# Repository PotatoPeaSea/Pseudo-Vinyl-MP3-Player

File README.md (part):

# Pseudo Vinyl MP3 Player

A portable, battery-powered MP3 player built on the **ESP32-WROVER N4R8** that streams audio wirelessly to Bluetooth earbuds and features a **vinyl-style spinning album art** animation on a circular display.

> [!NOTE]
> **Why the classic ESP32 and not the S3?** The project originally targeted the ESP32-S3, but the S3 only has BLE — **no Bluetooth Classic**, which A2DP audio streaming requires. The original ESP32 is the only chip in the family that can act as an A2DP source. The board started on a **WROOM-32** (no PSRAM, a hard ~250–290KB working-heap budget — see [`docs/MEMORY.md`](docs/MEMORY.md) for everything that constraint drove) and later moved to a **WROVER N4R8**, same classic-ESP32 die plus **8MB PSRAM**, which is now the current hardware target. Audio output is **Bluetooth-only** — the wired PCM5102 DAC path from early prototyping was removed once the BT stack needed the RAM it occupied, and hasn't come back now that PSRAM is available (out of scope, not a technical blocker).

## Features

- **Bluetooth Audio** — Streams to wireless earbuds/speakers via A2DP, with on-device scanning, pairing, and auto-reconnect. Bluetooth is the only output — there is no wired jack.
- **Circular Display** — 1.28" GC9A01 240×240 IPS round screen
- **Vinyl Spin Animation** — Album art spins like a vinyl record during playback at a true 60fps, with a progress ring around the display edge and a drop-shadowed title for legibility over any art color
- **Physical Controls** — 3 buttons (play/pause, next, previous) + rotary encoder (volume/scroll)
- **Shuffle & Repeat** — Normal / Shuffle / Repeat All / Repeat One, cycled via encoder push
- **SD Card Storage** — Recursively scans a FAT32 SD card for MP3s; the library and playlist list load automatically at boot, before any speaker connects
- **Folder Playlists** — Top-level SD card folders are selectable playlists, alongside an always-available "All Songs" library
- **Persistent Settings** — Volume and paired Bluetooth device survive power cycles (NVS)
- **Battery Powered** — LiPo battery with TP4056 USB-C charging

## Documentation

| Document | Contents |
|---|---|
| [User Guide](docs/USER_GUIDE.md) | Getting started, controls, pairing, troubleshooting |
| [PRD](docs/PRD.md) | Original requirements/pins/risks — WROOM-32 prototype era, not updated for the WROVER pin move |
| [MEMORY.md](docs/MEMORY.md) | Canonical hardware bring-up log — every RAM/BT/audio failure found on real hardware, root cause, and fix |
| [HANDOFF.md](docs/HANDOFF.md) | What's implemented-but-not-yet-hardware-verified right now |
| This README | System architecture, build instructions |

---

## Hardware

| Component | Model | Interface |
|---|---|---|
| MCU | ESP32-WROVER N4R8 (4MB flash, 8MB PSRAM) | — |
| Display | GC9A01 1.28" Round IPS, 240×240 | SPI (GPIO-matrix routed) |
| Storage | SPI SD card reader, FAT32 | SPI (HSPI) |
| Encoder | KY-040 rotary encoder | GPIO |
| Buttons | 3× tactile switches | GPIO |
| Battery | 3.7V LiPo + TP4056 USB-C charger | — |

### Enclosure and PCB

The enclosure is a three-part 3D print designed in Fusion 360: a case, a lid with a window for the round display, and separate arrow buttons. The source assembly (`.f3z`) and printable STLs are in [`CAD/`](CAD/).

The custom PCB is designed in KiCad 10. **[`MP3PlayerPCB_v2/`](MP3PlayerPCB_v2/)** is the current board: an AI-Thinker ESP32-CAM carrier with the GC9A01 display, a PCF8574 input expander for the encoder and buttons, and an AP2112K 3.3 V regulator, fully routed on 2 layers (68.4 x 38.5 mm). See its [README](MP3PlayerPCB_v2/README.md) for the pin map, verification results and enclosure fit notes.

The earlier v1 project ([`MP3PlayerPCB/`](MP3PlayerPCB/)) is kept for reference. Its schematic covers the MCU module, the GC9A01 display connector, the next/previous buttons and rotary encoder, and on-board TP4056 LiPo charging with charge and standby LEDs; v2 moves charging to an off-board TP4056 module.

### Wiring

**[`firmware/src/config.h`](firmware/src/config.h) is the source of truth for pins** — it's updated in lockstep with the firmware. [PRD §5](docs/PRD.md) still documents the original WROOM-32 prototype wiring and has not been updated for the WROVER pin move below; treat it as historical background, not a wiring reference.

| Peripheral | Pins |
|---|---|
| Display | MOSI 23, SCLK 19, CS 22, DC 21, RST 27 |
| SD card (SDMMC, 1-bit) | CLK 14, CMD 15, D0 2 |
| Encoder | CLK 32, DT 33, SW 5 |
| Buttons | Play 13, Next 18, Prev 4 |
| Battery sense | GPIO 34 (ADC1) |

Wiring rules worth knowing (all enforced by this pin map):

1. **GPIO 16/17 are reserved for PSRAM** (CS/CLK) on the WROVER and can't be used for anything else.
2. **SD card uses the SDMMC peripheral, not SPI.** On classic ESP32 its CLK/CMD/D0 pins are fixed in the IOMUX (not GPIO-matrix routable), so 14/15/2 aren't a preference — they're the only usable values in 1-bit mode. This also means GPIO 12 (SDMMC's D2 in 4-bit mode) is untouched: nothing drives it, so its old boot-strap risk (a pull-up there selects 1.8V flash voltage and bricks the board) no longer applies.
3. **Battery sense must be on ADC1** (GPIO 32–39). ADC2 is unusable while Bluetooth is running.
4. **Display is on its own SPI bus**, GPIO-matrix routed (no IOMUX-native pins were free) — if the panel tears or shows garbage, drop `SPI_FREQUENCY` from 40MHz to 27MHz before suspecting anything else. It no longer shares a bus with SD (SD is now SDMMC, a separate peripheral entirely), so display refresh never contends with audio streaming from the card.

---

## System Architecture

### Module layout

```
firmware/src/
├── main.cpp                  # Boot sequence + FreeRTOS tasks + input routing
├── config.h                  # All pins, buffer sizes, tunables
├── audio/audio_manager.*     # MP3 decode (helix), playlist, output routing
├── bluetooth/bt_manager.*    # A2DP source, discovery, PCM ring buffer, NVS
├── display/display_manager.* # TFT_eSPI + LVGL glue, draw buffers
├── display/ui_manager.*      # All LVGL screens, virtual keypad, album art
├── input/input_manager.*     # Debounced buttons + quadrature encoder ISR
└── storage/sd_manager.*      # SD mount, recursive MP3 scan, playlist folders, .art loading
```

Each module is a namespace with a small public API (`AudioMgr::`, `BtMgr::`, `UI::`, …); `main.cpp` is the only place that wires them together.

### Task model (dual-core FreeRTOS)

```mermaid
graph LR
    subgraph Core 0
        BT["BT Classic stack<br/>(controller + Bluedroid host + SBC encode)"]
    end
    subgraph Core 1
        AUDIO["audio task (prio 3)<br/>SD read → helix MP3 decode<br/>→ volume → BT ring buffer"]
        INPUT["input task (prio 2)<br/>5ms poll, debounce,<br/>event routing"]
        UI["ui task (prio 1)<br/>LVGL refresh @ true 60Hz<br/>vinyl spin, BT status sync"]
    end
    AUDIO -- "PCM ring buffer (10KB)" --> BT
    INPUT -- "LVGL keys / AudioMgr calls" --> UI
```

Core 0 is Bluetooth-only by design: SD/decode flash-cache pressure sharing a core with the BT stack was a measured source of L2CAP congestion (audio stutter), so all three of this project's own tasks — audio, input, UI — run on core 1, with audio at the highest priority of the three (dropped frames beat dropped audio).

- **Audio task (core 1, prio 3)** runs the decode loop: one `StreamCopy` step per iteration reads MP3 bytes from SD, decodes via helix, applies volume, and writes PCM into the ring buffer that feeds Bluetooth. Decode preempts LVGL rendering, which shares the core at a lower priority.
- **UI task (core 1, prio 1)** drives LVGL: syncs now-playing state, spins the vinyl, and polls Bluetooth state a few times per second (not every frame).
- **Input task (core 1, prio 2)** polls buttons/encoder every 5ms with 50ms debounce and routes events based on the active screen.

### Audio pipeline

```
              ┌────────────────────────── audio task (core 1) ──────────────────────────┐
SD card ──> MP3 file ──> StreamCopy ──> helix MP3 decoder ──> meter ──> VolumeStream ──> BtPrint
                                                                                             │
                                                                                             ▼
                                                                        PCM ring buffer (10KB, BtMgr)
                                                                                             │ (pulled by BT task, core 0)
                                                                                             ▼
                                                                              A2DP source → earbuds
```

Key decisions:

- **helix MP3 (arduino-audio-tools)** instead of ESP32-audioI2S: the latter requires PSRAM as of v3.x, which the original WROOM-32 target didn't have. Helix decodes in ~25KB and is now allocated once at boot and kept resident for the app's lifetime (re-allocating it at play time raced other allocations and lost, on hardware — see `docs/MEMORY.md`).
- **Bluetooth is the only output.** A wired PCM5102 I2S path existed during early prototyping and was removed once it couldn't fit next to the BT stack on the no-PSRAM board; it hasn't been reinstated now that the WROVER has PSRAM to spare (possible follow-up, not implemented).
- **Position/duration are derived, not parsed from ID3/Xing headers.** Position = decoded PCM bytes ÷ byte rate. Duration is an estimate — position × file size ÷ compressed bytes consumed so far — computed **once** after a brief warm-up (enough decoded seconds + bytes consumed to get a reliable sample) and then held static for the rest of the track, rather than continuously recomputed: a song's duration doesn't change while it plays, so freezing the estimate once trumps chasing a "more accurate" live number. Two earlier attempts at keeping it live and smoothing the noise both proved visibly unstable on hardware — see `docs/HANDOFF.md` for that history if this needs revisiting.
- **With no BT sink connected, playback holds** rather than racing through the file while writes are dropped.
- A2DP is fixed at 44.1kHz — MP3s at other sample rates play off-speed over Bluetooth.

### Bluetooth design

`BtMgr` wraps `BluetoothA2DPSource` (pschatzmann/ESP32-A2DP):

- While unconnected, the library continuously discovers nearby A2DP sinks; every device seen is collected for the UI list.
- Selecting a device sets it as the **target** — the next discovery hit on that name connects, and the name is persisted to NVS so the player auto-reconnects on later boots.
- The BT stack pulls PCM from the ring buffer on its own task; underruns are zero-filled so the stream never stalls.

### Display & UI

- **TFT_eSPI** drives the GC9A01 at 40MHz (GPIO-matrix routed, see the wiring notes above); **LVGL 8** renders into a single 240×80 draw buffer (38.4KB) in internal DMA-capable RAM. Single-buffered on purpose: the flush callback is a blocking SPI write with no DMA handoff, so a second buffer would cost RAM with nothing to render into concurrently — the available headroom went into one bigger buffer (fewer flush strips per frame) instead.
- `LV_DISP_DEF_REFR_PERIOD` is pinned to 16ms to match the UI task's own refresh cadence — left unset, LVGL's internal default (30ms/~33fps) silently drops half the vinyl-spin animation's angle steps even though the app-level state updates at 60Hz.
- `LV_COLOR_16_SWAP=1` produces SPI byte order directly, so the flush callback pushes pixels without a per-frame swap.
- **Lazy screen lifecycle:** only the currently active screen's LVGL widget tree exists at any time — screens are built on show and deleted on switch, deferred to the UI task so a callback never deletes the screen it's running inside. Slower screen changes, near-zero idle footprint.
- **Navigation without a touchscreen:** a virtual LVGL *keypad* input device. The input task translates encoder turns into `LV_KEY_NEXT/PREV` (focus movement) and the Play button into `LV_KEY_ENTER` (select) whenever a menu screen is active. Each screen has its own LVGL focus group.
- **Album art** is a pre-scaled raw RGB565 file (`.art`), loaded once per track change and freed when leaving Now Playing, displayed inside a circle-clipped holder with the title given a duplicate-label drop shadow for legibility over unpredictable art colors. See the art tool below.
- Five screens: Library, Playlists, Settings, Bluetooth, Now Playing — cycled with Next/Previous.

### Memory budget (PSRAM-backed, but Bluetooth still lives in internal SRAM)

The board moved from a no-PSRAM WROOM-32 (~250–290KB usable internal SRAM, every allocation fighting for the same pool) to a WROVER N4R8 with 8MB PSRAM. The Arduino framework here is built with `CONFIG_SPIRAM_MALLOC_ALWAYSINTERNAL=4096`, so **ordinary `malloc`/`new` over 4KB lands in PSRAM automatically** — LVGL widget trees, the song/playlist vectors, and album art buffers stop competing with Bluetooth for internal RAM without any code changes. Allocations that must stay internal (Bluedroid, the LVGL draw buffer — ESP32 SPI DMA can't read PSRAM) request that capability explicitly.

| Consumer | Heap | ~Size |
|---|---|---|
| BT Classic stack (controller + Bluedroid) | internal | ~120KB to initialize, ~108KB retained |
| helix MP3 decoder (resident from boot) | internal | ~25KB |
| LVGL draw buffer (single, 240×80) | internal (DMA) | 38.4KB |
| BT PCM ring buffer | internal | 10KB |
| Album art (≤240×240 RGB565, `ART_MAX_SIDE`) | PSRAM | ≤112.5KB |
| LVGL widget trees, song/playlist vectors | PSRAM | small, no longer RAM-critical |

Measured on real hardware (`docs/MEMORY.md` has the full bring-up log): after BT init + SD mount + a full 15-song library, internal SRAM sits around **free≈68–82KB, largest contiguous block≈59–82KB** — comfortably clear of the ~50KB the A2DP connection handshake needs, which used to be the tightest margin on the WROOM-32 (~20KB largest there). Measured at build: **16.5% static RAM, 52.6% flash**.

---

## Building the Firmware

Requires [PlatformIO](https://platformio.org/).

```bash
cd firmware
pio run                 # build
pio run -t upload       # flash over USB
pio device monitor      # serial log @ 115200
```

The environment is `esp32dev` (see [`firmware/platformio.ini`](firmware/platformio.ini)). Libraries: TFT_eSPI, LVGL 8.3, arduino-audio-tools, arduino-libhelix, ESP32-A2DP. The 3MB `huge_app` partition is used (no OTA) because BT Classic + LVGL + codecs don't fit the default scheme.

### Debug environment (no hardware needed)

`esp32dev-debug` extends `esp32dev` with `DEBUG_MODE=1` — the serial console simulates buttons/encoder input, so you can exercise the UI without wiring up physical controls.

```bash
cd firmware
pio run -e esp32dev-debug              # build only
pio run -e esp32dev-debug -t upload    # build + flash over USB
pio device monitor                     # serial log @ 115200 (simulated input + [SD]/[BT]/[Audio]/[UI] logs)
```

## Album Art Pre-Scaler Tool

MP3 album art is prepared on your PC before copying music to the SD card — the device never decodes JPEG/PNG.

```bash
cd tools/prescale_art
pip install -r requirements.txt
python prescale_art.py /path/to/music
```

For each `song.mp3` with embedded art, this writes `song.art` alongside it: a raw 90×90 RGB565 bitmap by default (16,200 bytes, big-endian to match the firmware's `LV_COLOR_16_SWAP`) — 90px matches the on-screen vinyl label, so larger art is just downscaled at display time and 90px keeps files small. A GUI version (`prescale_art_gui.py`) is also available. The firmware accepts anything up to 240×240 (`ART_MAX_SIDE`, the display's native resolution); `--size` is capped at 240 since nothing larger is ever useful.

## Project Structure

```
Pseudo-Vinyl-MP3-Player/
├── README.md                # This file — architecture + build guide
├── docs/
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
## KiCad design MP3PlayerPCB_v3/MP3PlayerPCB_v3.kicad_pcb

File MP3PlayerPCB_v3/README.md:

# MP3PlayerPCB v3: ESP32-WROVER main board

v3 is a separate KiCad project. `../MP3PlayerPCB_v2/` (ESP32-CAM carrier) is left untouched.

**Status: designed and checked in KiCad, not built.** Nothing here has been tested on hardware, and the firmware changes below are not done yet.

## What's on the board

| Ref | Part | Notes |
|---|---|---|
| U1 | ESP32-WROVER-E-N4R8 | Soldered directly. Classic ESP32, so Bluetooth A2DP still works. 4 MB flash, 8 MB PSRAM |
| J6 | Hirose DM3AT microSD | SDMMC 1-bit, same pins as the current firmware |
| U8 | PCM5102A DAC | I2S, generates its own clock, so no MCLK pin is needed |
| U9 | TPA6132A2 headphone amp | Ground-referenced, so no output capacitors. Set to -6 dB |
| J3 | USB-C, analog audio | Passive USB-C earbuds only (see below) |
| J4 | Same Sky SJ-3524-SMT | 3.5 mm headphone jack with plug detect |
| U2 | MCP73831 charger | 500 mA (R5 = 2k). Raise R5 for cells under 500 mAh |
| D4 / D5 | Red / green LED | Red while charging, green when full |
| Q1, D1 | Power path | On USB the load runs from USB and the battery only charges, so charge termination works |
| U5 | MAX17048 fuel gauge | I2C 0x36, wired straight to the cell |
| U3 / U4 | AP2112K-3.3 | Digital 3V3 / separate quiet analog rail that firmware can turn off |
| SW4 | C&K OS102011MA1Q | Power switch. Cuts the load only; charging still works when off |
| J2 | USB-C, charge + data | Charging, flashing and serial console |
| U6, Q2, Q3 | CH340C + auto-program | Flash over USB-C with no buttons or adapter |
| J1 | 1x7 socket, 2.54 mm | Plug-in header for the same GC9A01 module used on v2 |
| Q4 | Display power switch | Turns the panel and its always-on backlight off |
| SW1 / SW2 | 6x6 tact, 13 mm | NEXT / PREV, same spacing as v2 |
| SW3 | Alps EC11E + switch | Volume / scroll / press |
| SW5 / SW6 | KMR2 tact | BOOT / RESET |
| J5 | JST-PH 2-pin | LiPo. **Check your cell's polarity against the silkscreen first; JST leads are not standardized** |

Board: 86 x 50 mm, 4 layers (signal / GND / 3V3 / signal), all parts on the top side. 0.2 mm signals, 0.5 mm power, 0.6/0.3 mm vias, 0.15 mm clearance. Copper keep-out on all layers under the antenna, which sits outside the display's footprint.

## USB-C earbud compatibility

J3 is wired for USB-C Audio Accessory Mode: left and right on D-/D+, ground on the SBU pins.

- **Works:** passive (analog) USB-C earbuds and anything with a 3.5 mm plug.
- **Does not work:** digital USB-C earbuds with a built-in DAC, which is most of them, including many sold with phones. They need a USB host, and the classic ESP32 doesn't have one. The ESP32-S3 does, but it has no Bluetooth Classic, so A2DP would be lost.

## Pin map

| GPIO | Use | | GPIO | Use |
|---|---|---|---|---|
| 19 / 23 / 22 / 21 / 27 | TFT SCLK / MOSI / CS / DC / RST | | 25 / 26 / 13 | I2S LRCK / BCK / DOUT |
| 14 / 15 / 2 | SD CLK / CMD / D0 | | 12 | AUDIO_EN (high = analog on) |
| 32 / 33 | Encoder A / B | | 18 | TFT_PWR (high = panel off) |
| 36 | Encoder switch | | 4 / 5 | I2C SDA / SCL |
| 35 / 39 | NEXT / PREV | | 34 | HP_DET (low = earbuds in, either port) |
| 1 / 3 | UART0 to CH340C | | 0 | BOOT, keep as input at runtime |

## Firmware changes needed

Display, SD and encoder A/B pins are unchanged. `config.h` needs:

- Move `PIN_ENC_SW` 5 to 36, `PIN_BTN_NEXT` 18 to 35, `PIN_BTN_PREV` 4 to 39.
- Remove `PIN_BTN_PLAY` (GPIO 13 is now I2S) and map play/pause onto the encoder press.
- Remove `PIN_BATT_ADC` and read the MAX17048 over I2C instead.
- Add the wired audio path: I2S output, AUDIO_EN, HP_DET, and software volume (the DAC has none).
- GPIO 12 is a strapping pin. Only drive AUDIO_EN after boot.
- Before setting TFT_PWR high, set the TFT pins low or to inputs so the panel isn't back-powered. Re-run panel init after power-up.

## Verification (KiCad 10.0.5)

- **ERC:** 0 errors, 2 warnings (SBU pins deliberately tied to ground).
- **DRC:** 0 errors, 0 unconnected, 0 schematic-parity issues. 4 warnings: the stock USB-C footprints' silkscreen crosses the board edge, as edge connectors do.
- KiCad's exported netlist matches the design data on every named net.
- IC pinouts checked against manufacturer datasheets and, where KiCad has a symbol, against that too.
- WROVER footprint built from Espressif's land pattern (datasheet v2.4, Figure 15).

## Check before ordering

1. **J1 pin order** against your display module (VCC, GND, SCL, SDA, DC, CS, RST, carried over from v2).
2. **J4 tip switch:** the jack datasheet could not be retrieved. Confirm TN is the normally-closed tip contact, or plug detect on the 3.5 mm jack won't work.
3. **D6 / D7** must be bidirectional TVS diodes. A normal USB ESD part would clip the audio.
4. **Battery:** must have a built-in protection circuit. The board has no over-discharge or short-circuit cutoff.
5. **Assembly:** U9 (QFN) and U5 (DFN) can't reasonably be hand-soldered. Use PCBA or a hot plate and stencil.

## Enclosure

The existing case won't fit. A new one needs openings for J2 and SW4 (top edge), J3, J4 and J6 (bottom edge). The button, encoder and display spacing matches v2, so the lid layout carries over. The display now plugs into a socket, so it sits higher than v2 and is only held along one edge: add a printed support under its far side.

`U1`'s 3D model is a stretched WROOM stand-in (KiCad ships no WROVER model); it only affects renders.

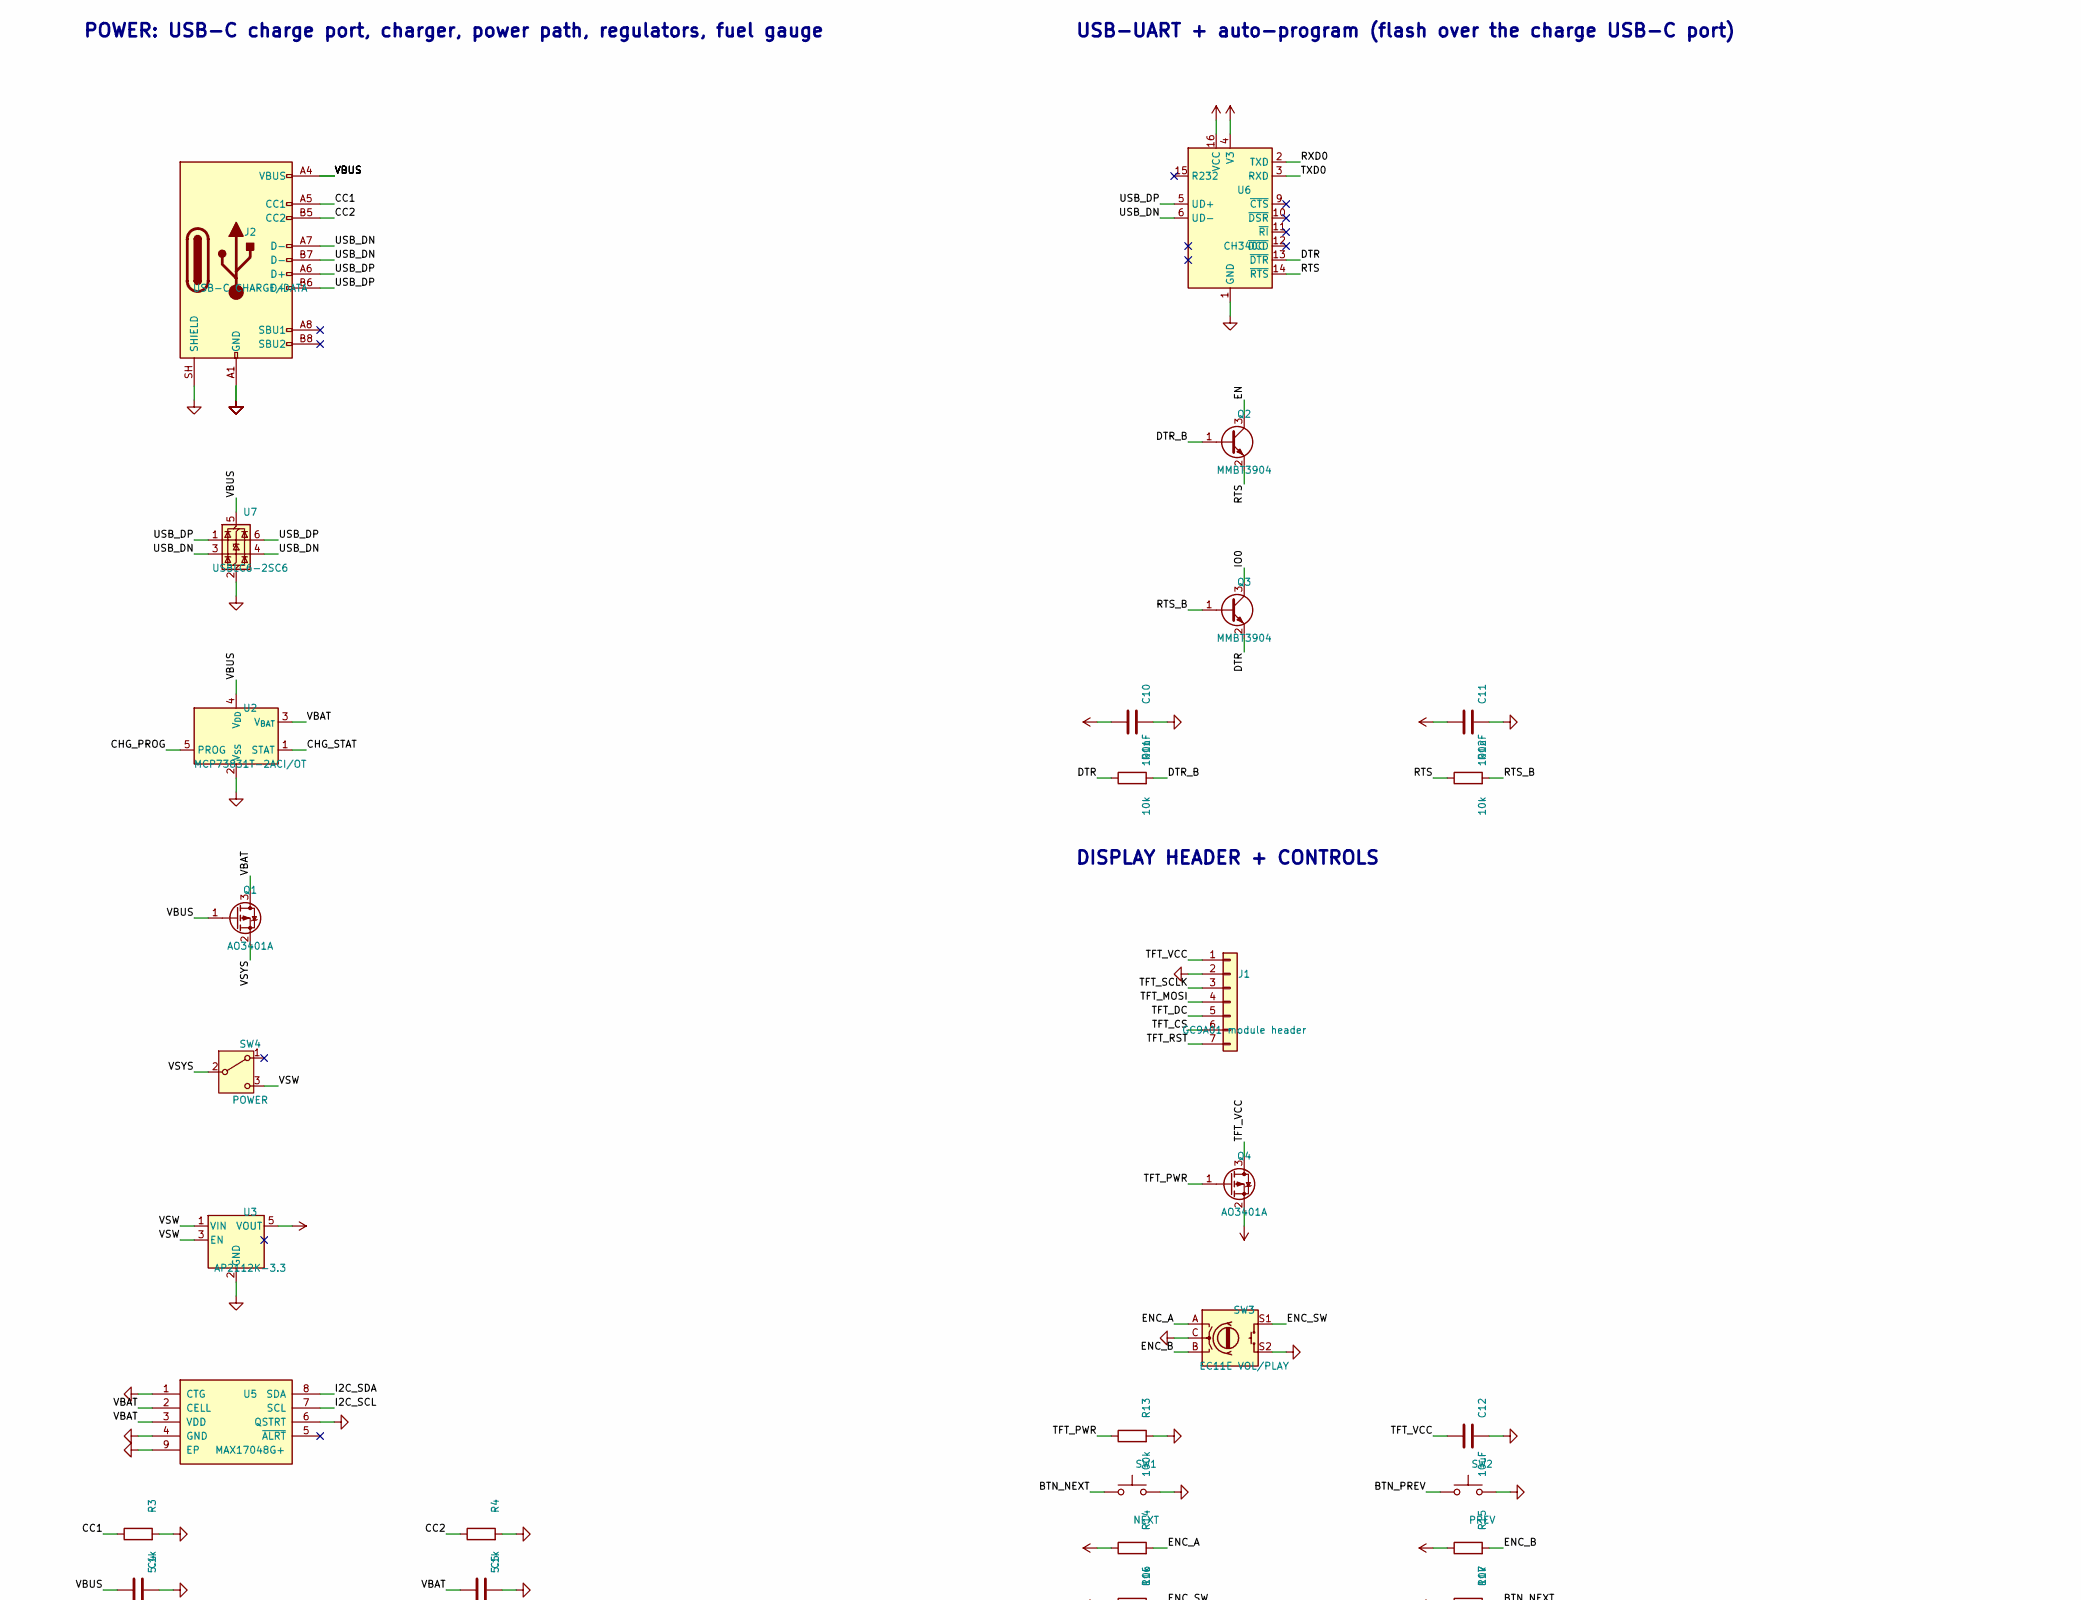
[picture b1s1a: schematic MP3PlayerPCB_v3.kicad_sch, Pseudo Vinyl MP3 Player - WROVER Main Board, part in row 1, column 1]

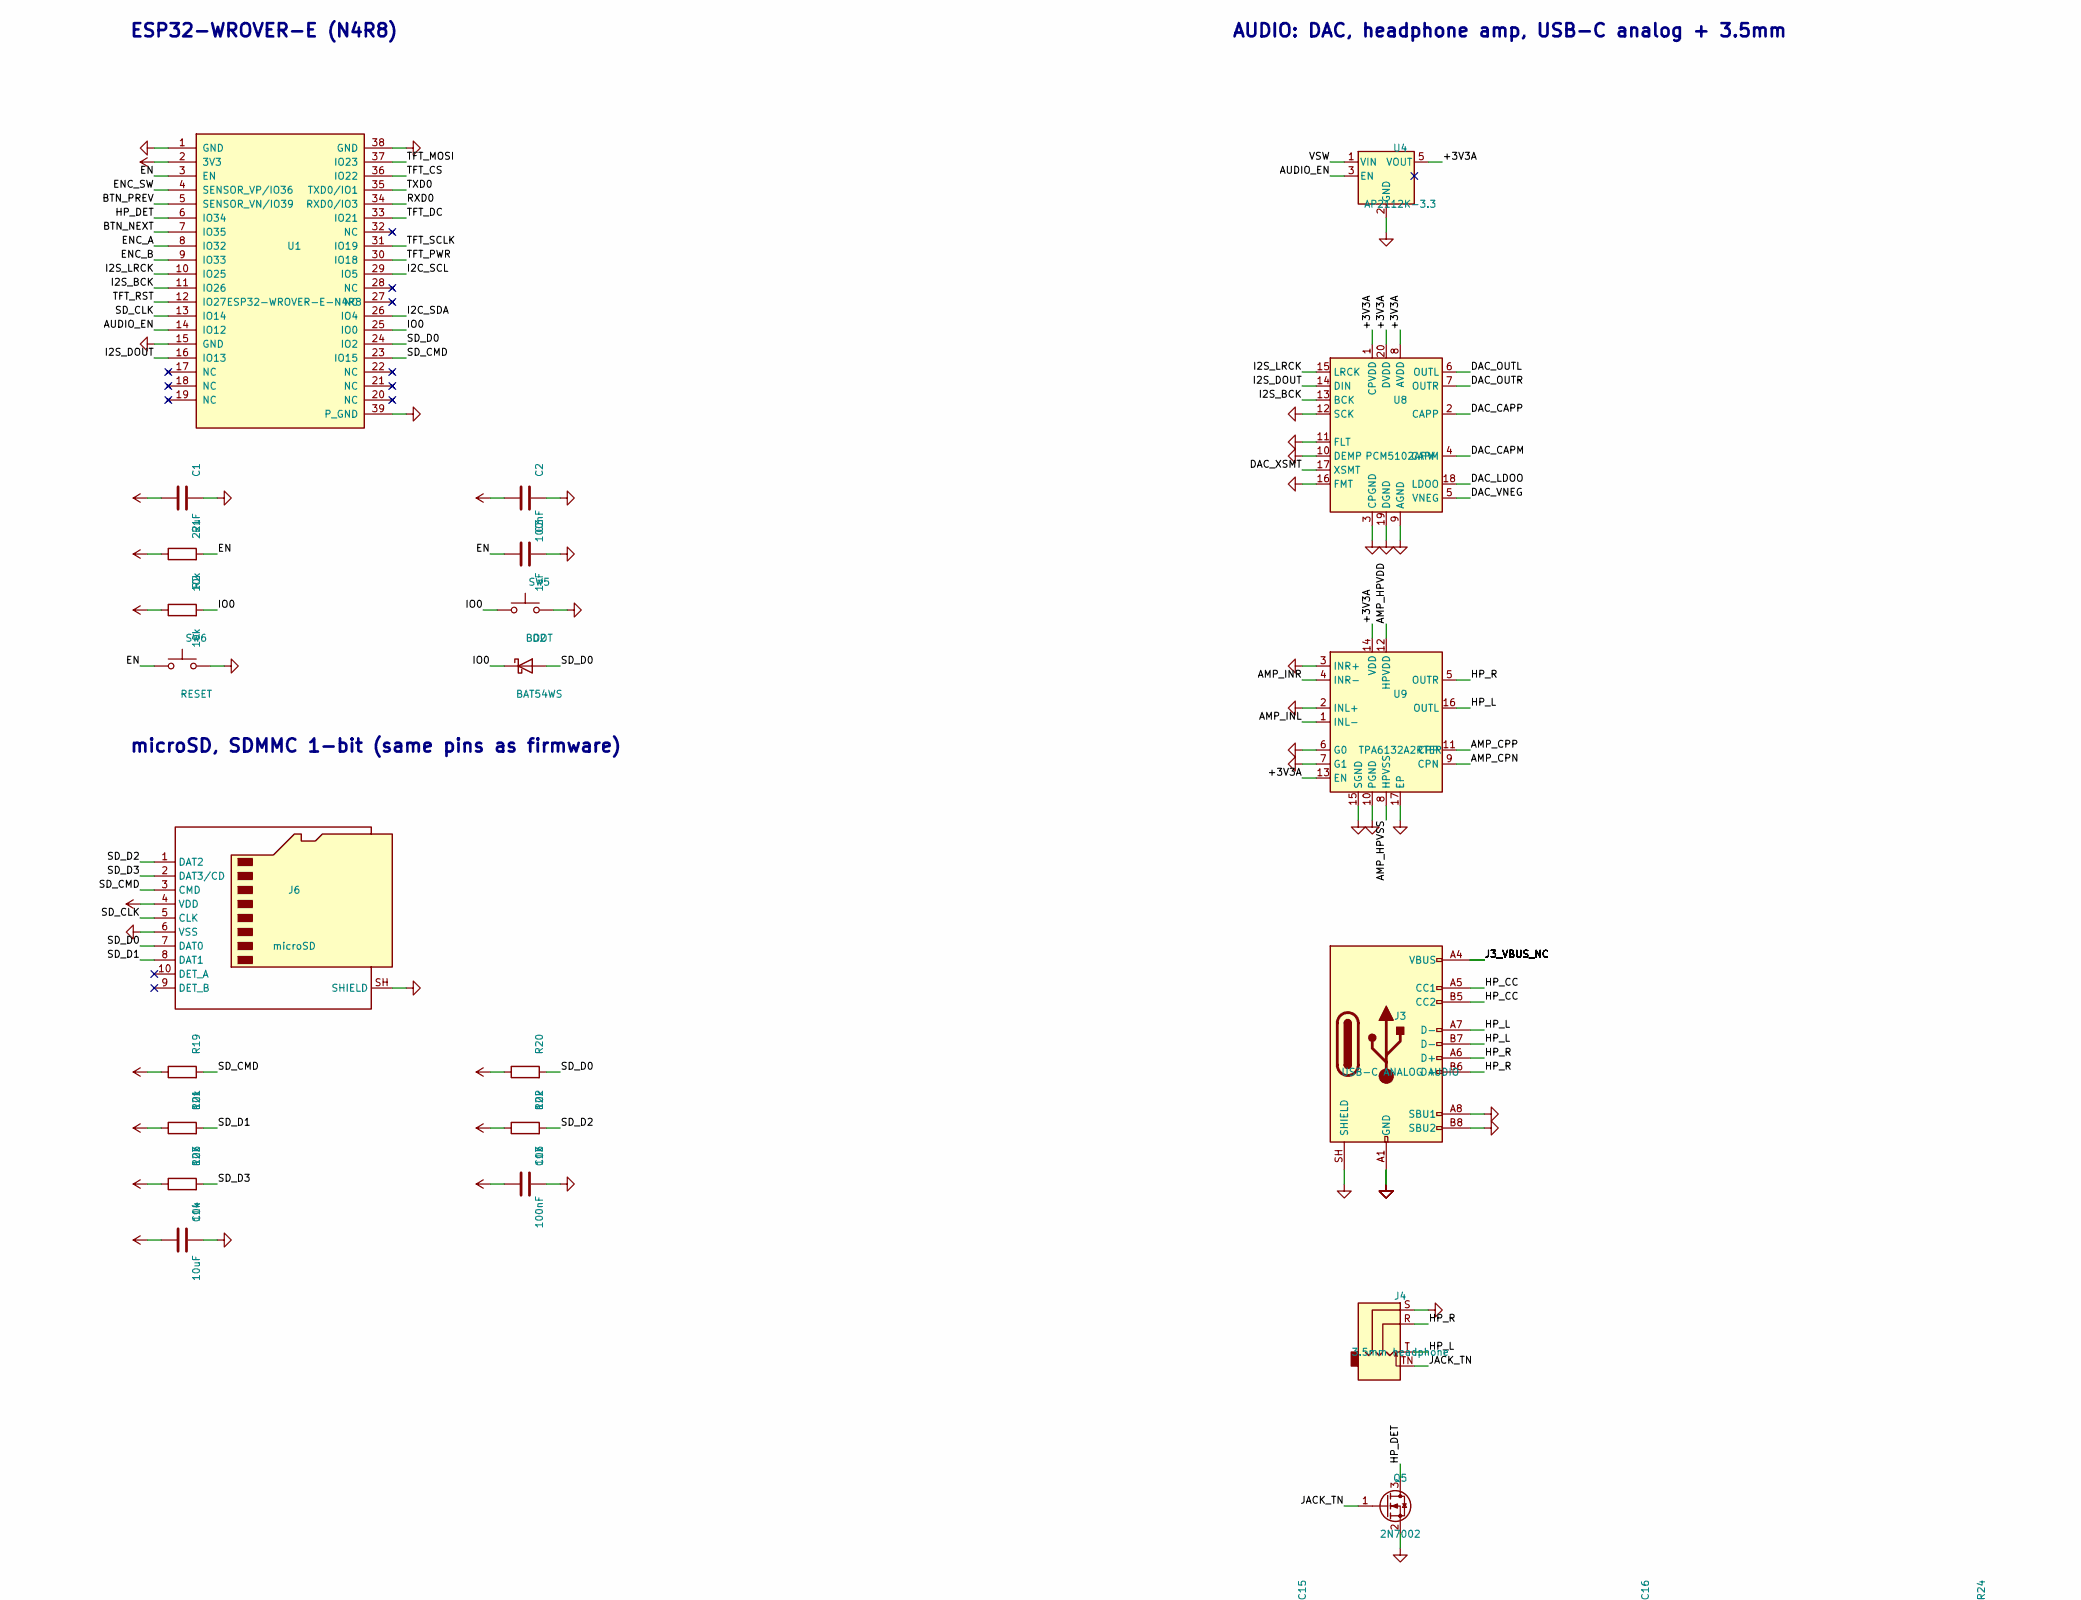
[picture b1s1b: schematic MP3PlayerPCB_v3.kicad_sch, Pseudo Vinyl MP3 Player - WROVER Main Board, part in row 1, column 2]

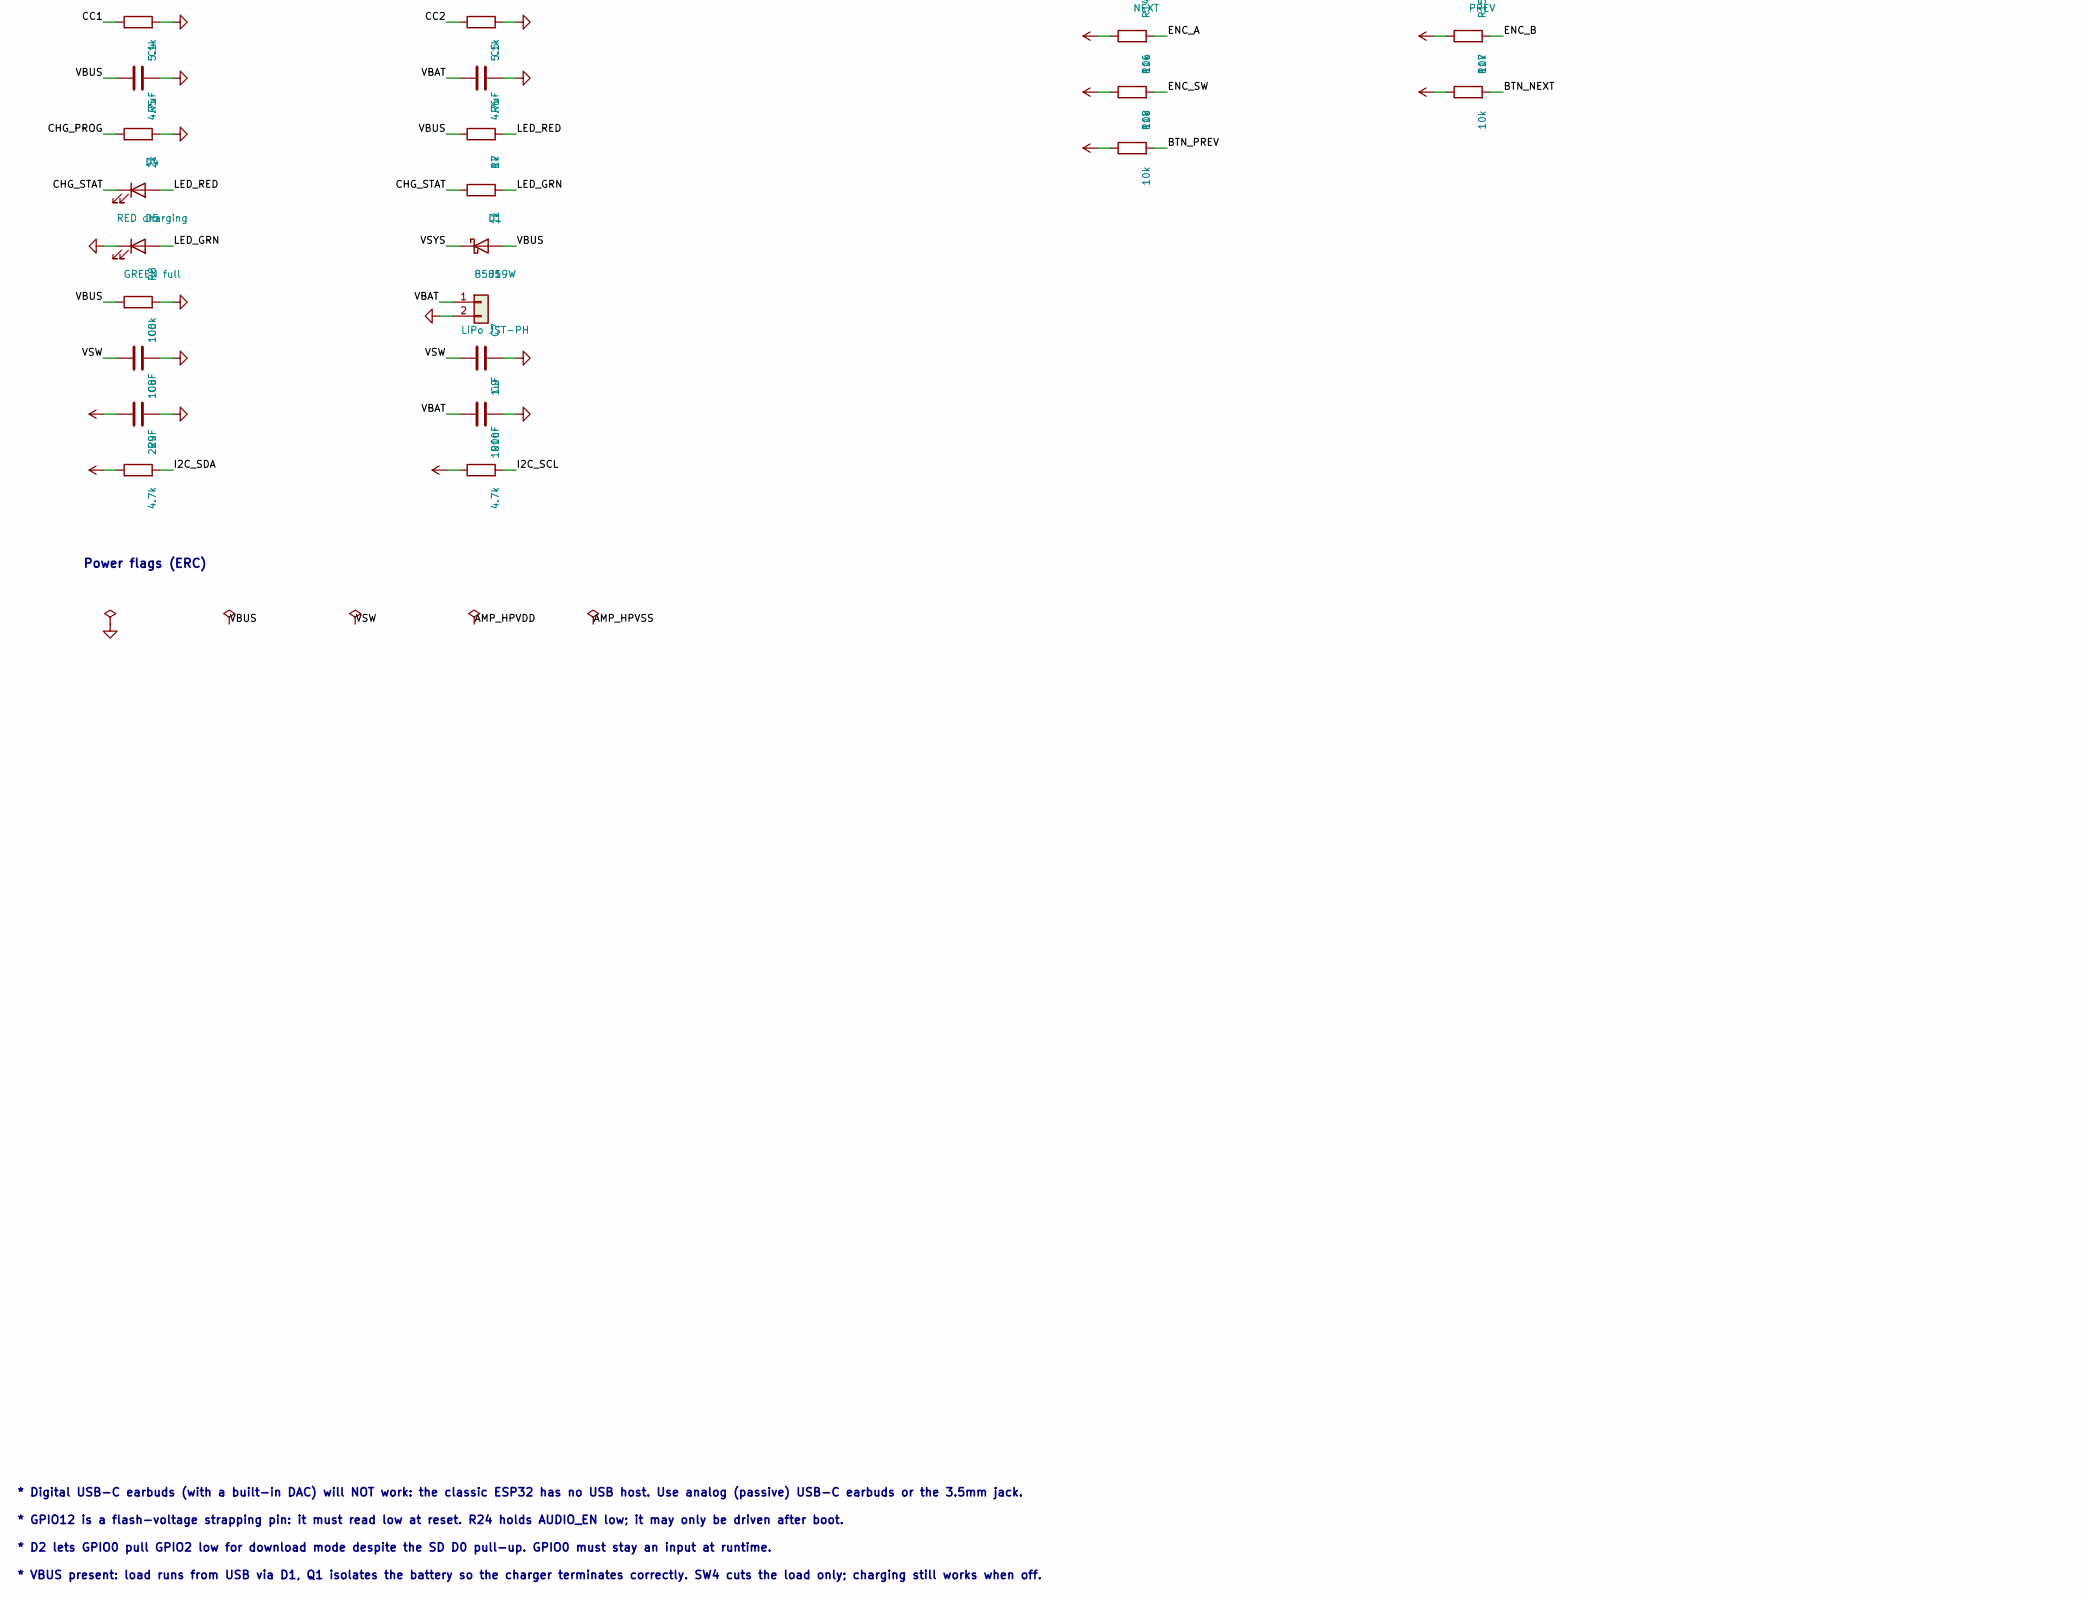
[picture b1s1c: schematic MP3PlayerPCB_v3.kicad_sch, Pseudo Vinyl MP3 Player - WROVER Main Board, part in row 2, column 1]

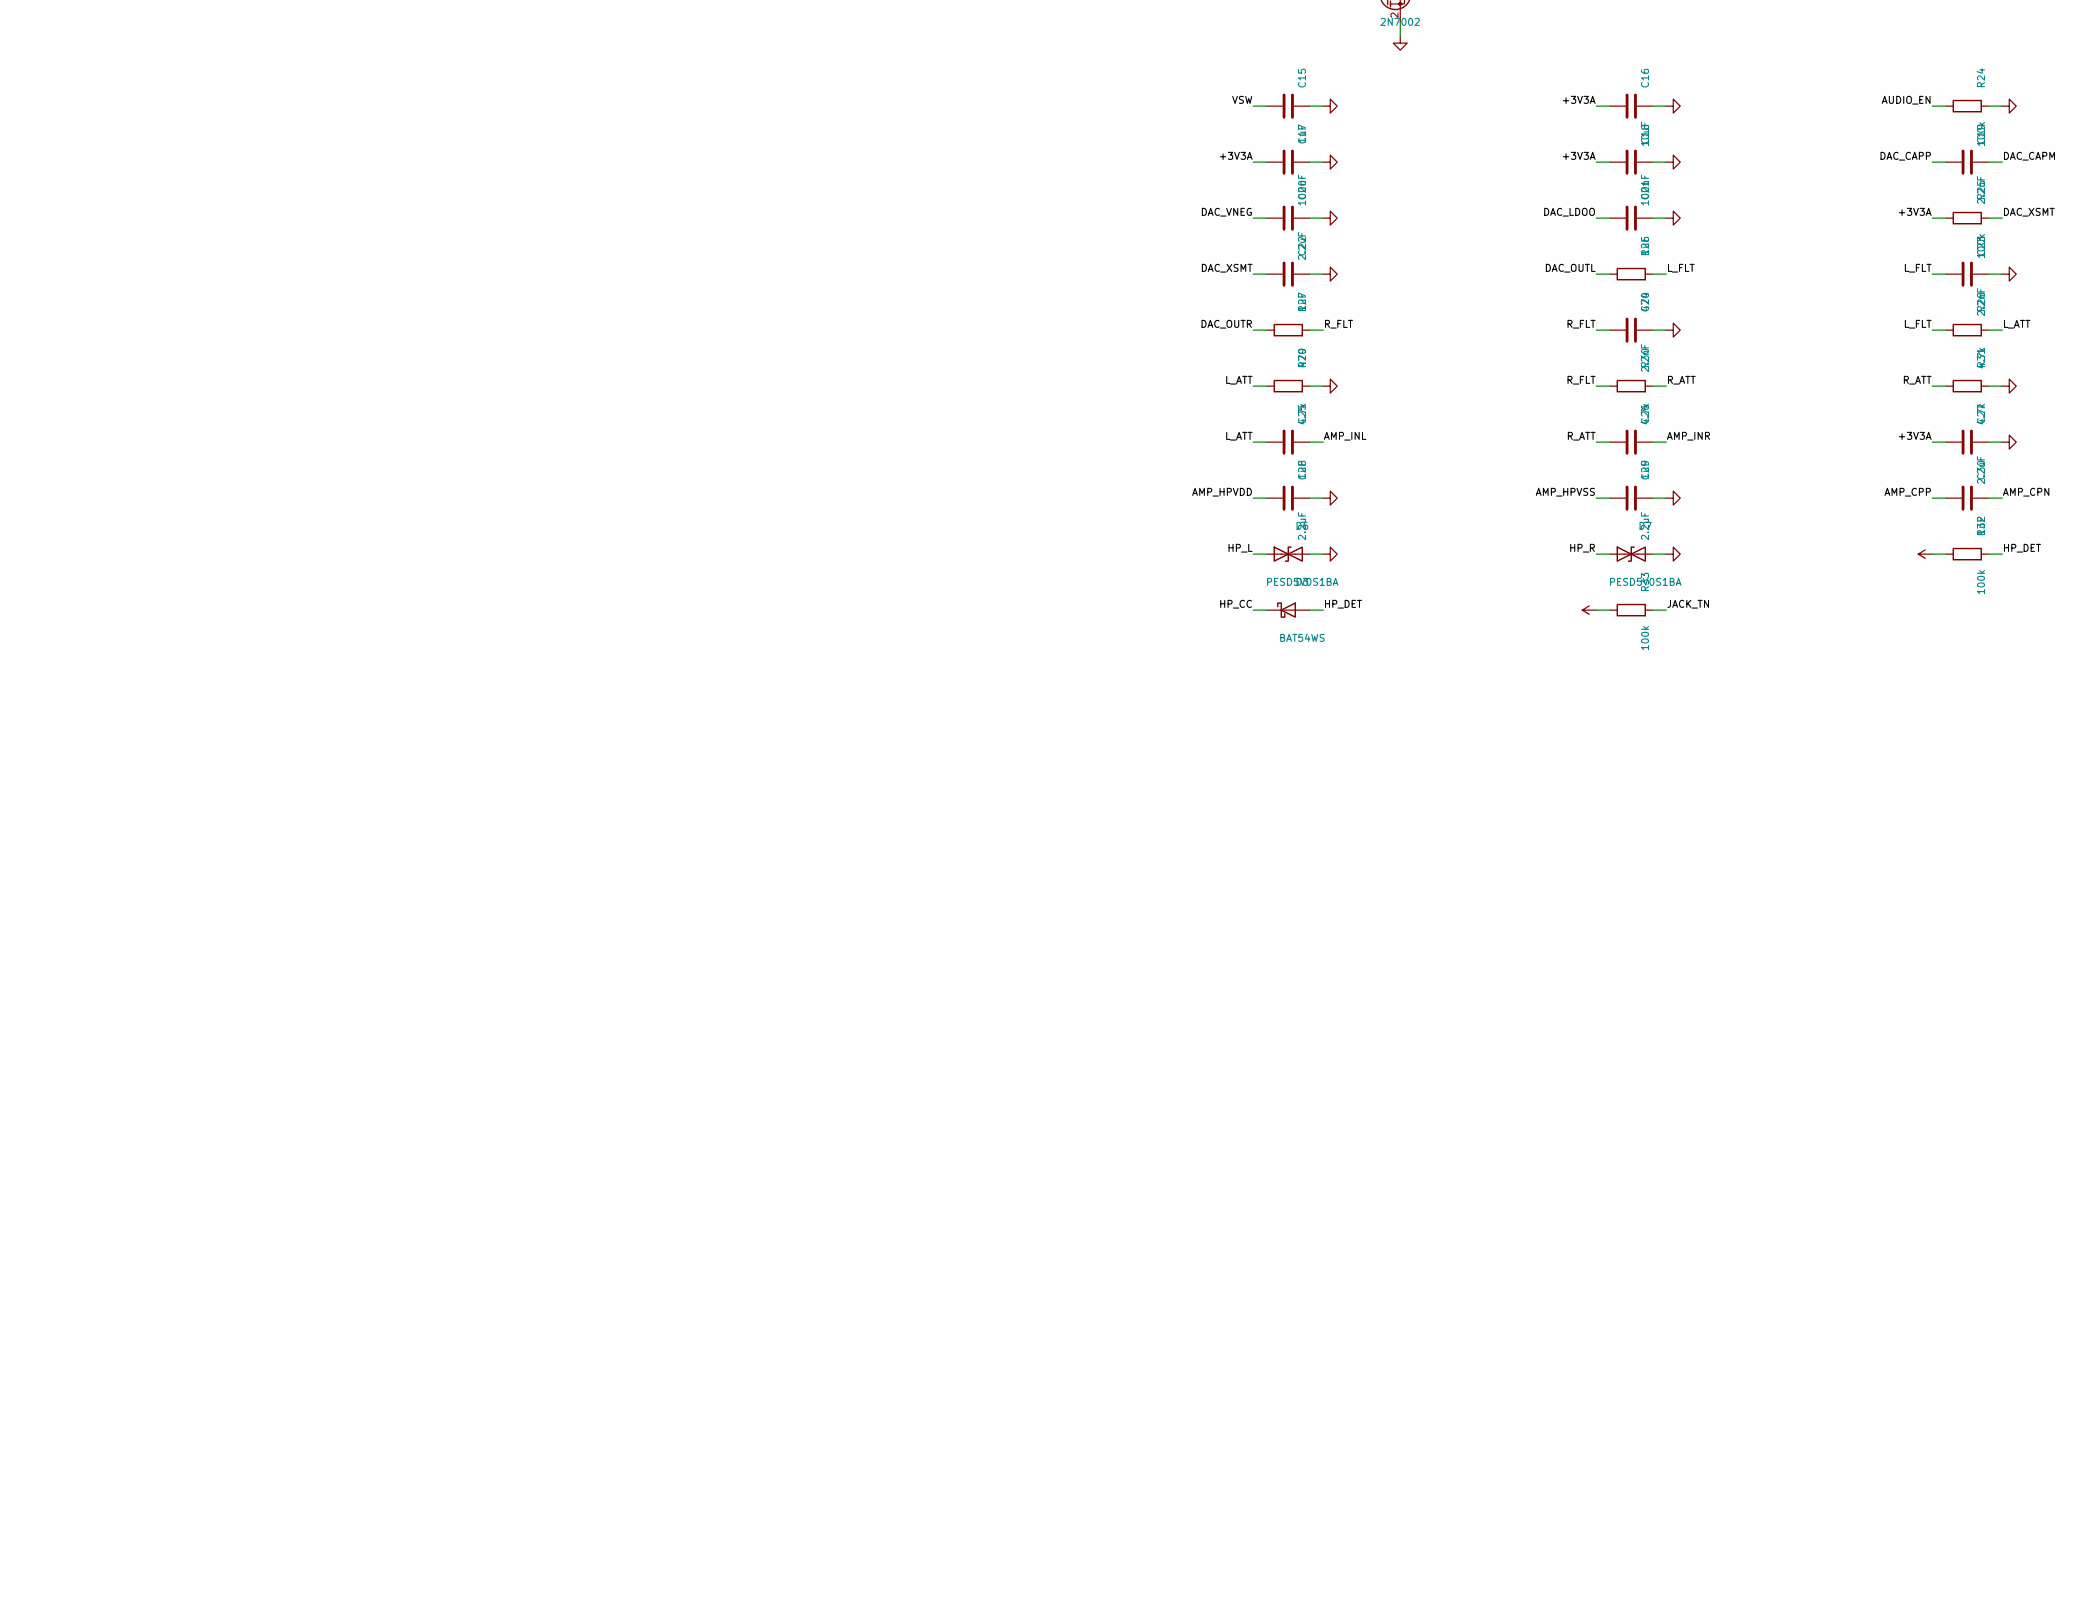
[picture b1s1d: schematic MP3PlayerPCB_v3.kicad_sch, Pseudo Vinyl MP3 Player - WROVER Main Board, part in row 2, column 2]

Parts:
C1, C8: 22uF; C_0805_2012Metric
C2, C9, C10, C11, C13, C17, C18: 100nF; C_0603_1608Metric
C3, C7, C15, C21, C22, C25, C26, C30: 1uF; C_0603_1608Metric
C4, C5: 4.7uF; C_0805_2012Metric
C6, C12, C14, C16: 10uF; C_0805_2012Metric
C19, C20, C27, C28, C29: 2.2uF; C_0603_1608Metric
C23, C24: 2.2nF; C_0603_1608Metric
D1: B5819W; D_SOD-123
D2, D3: BAT54WS; D_SOD-323
D4: RED charging; LED_0603_1608Metric
D5: GREEN full; LED_0603_1608Metric
D6, D7: PESD5V0S1BA; D_SOD-323
J1: GC9A01 module header; GC9A01_Header_1x07; MPN 2.54mm 1x7 female socket
J2: USB-C CHARGE/DATA; USB_C_Receptacle_HRO_TYPE-C-31-M-12; MPN HRO TYPE-C-31-M-12
J3: USB-C ANALOG AUDIO; USB_C_Receptacle_HRO_TYPE-C-31-M-12; MPN HRO TYPE-C-31-M-12
J4: 3.5mm headphone; Jack_3.5mm_CUI_SJ-3524-SMT_Horizontal; MPN Same Sky SJ-3524-SMT-TR
J5: LiPo JST-PH; JST_PH_S2B-PH-SM4-TB_1x02-1MP_P2.00mm_Horizontal; MPN JST S2B-PH-SM4-TB
J6: microSD; microSD_HC_Hirose_DM3AT-SF-PEJM5; MPN Hirose DM3AT-SF-PEJM5
Q1, Q4: AO3401A; SOT-23
Q2, Q3: MMBT3904; SOT-23
Q5: 2N7002; SOT-23
R1, R2, R11, R12, R14, R15, R16, R17, R18, R19, R20, R21, R22, R23: 10k; R_0603_1608Metric
R3, R4: 5.1k; R_0603_1608Metric
R5: 2k; R_0603_1608Metric
R6, R7: 1k; R_0603_1608Metric
R8, R13, R24, R25, R32, R33: 100k; R_0603_1608Metric
R9, R10, R28, R29, R30, R31: 4.7k; R_0603_1608Metric
R26, R27: 470; R_0603_1608Metric
SW1: NEXT; SW_PUSH_6mm_H13mm
SW2: PREV; SW_PUSH_6mm_H13mm
SW3: EC11E VOL/PLAY; RotaryEncoder_Alps_EC11E-Switch_Vertical_H20mm
SW4: POWER; SW_Slide_SPDT_Angled_CK_OS102011MA1Q; MPN C&K OS102011MA1Q
SW5: BOOT; SW_Push_1P1T_NO_CK_KMR2
SW6: RESET; SW_Push_1P1T_NO_CK_KMR2
U1: ESP32-WROVER-E-N4R8; ESP32-WROVER-E; MPN ESP32-WROVER-E-N4R8
U2: MCP73831T-2ACI/OT; SOT-23-5
U3, U4: AP2112K-3.3; SOT-23-5
U5: MAX17048G+; TDFN-8-1EP_2x2mm_P0.5mm_EP0.8x1.2mm; MPN MAX17048G+T10
U6: CH340C; SOIC-16_3.9x9.9mm_P1.27mm
U7: USBLC6-2SC6; SOT-23-6
U8: PCM5102APW; TSSOP-20_4.4x6.5mm_P0.65mm
U9: TPA6132A2RTER; Texas_RTE_WQFN-16-1EP_3x3mm_P0.5mm_EP1.2x0.8mm_ThermalVias

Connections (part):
+3V3: C1.1, C2.1, C8.1, C10.1, C11.1, C13.1, C14.1, J6.4 (VDD), Q4.2 (S), R1.1, R2.1, R9.1, R10.1, R14.1, R15.1, R16.1, R17.1, R18.1, R19.1, R20.1, R21.1, R22.1, R23.1, R32.1, R33.1, U1.2 (3V3), U3.5 (VOUT), U6.4 (V3), U6.16 (VCC)
/+3V3A: C16.1, C17.1, C18.1, C27.1, R25.1, U4.5 (VOUT), U8.1 (CPVDD), U8.8 (AVDD), U8.20 (DVDD), U9.13 (EN), U9.14 (VDD)
/AMP_CPN: C30.2, U9.9 (CPN)
/AMP_CPP: C30.1, U9.11 (CPP)
/AMP_HPVDD: C28.1, U9.12 (HPVDD)
/AMP_HPVSS: C29.1, U9.8 (HPVSS)
/AMP_INL: C25.2, U9.1 (INL-)
/AMP_INR: C26.2, U9.4 (INR-)
/AUDIO_EN: R24.1, U1.14 (IO12), U4.3 (EN)
/BTN_NEXT: R17.2, SW1.1, U1.7 (IO35)
/BTN_PREV: R18.2, SW2.1, U1.5 (SENSOR_VN/IO39)
/CC1: J2.A5 (CC1), R3.1
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
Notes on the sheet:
POWER: USB-C charge port, charger, power path, regulators, fuel gauge
USB-UART + auto-program (flash over the charge USB-C port)
DISPLAY HEADER + CONTROLS
ESP32-WROVER-E (N4R8)
microSD, SDMMC 1-bit (same pins as firmware)
AUDIO: DAC, headphone amp, USB-C analog + 3.5mm
Power flags (ERC)
* Digital USB-C earbuds (with a built-in DAC) will NOT work: the classic ESP32 has no USB host. Use analog (passive) USB-C earbuds or the 3.5mm jack.
* GPIO12 is a flash-voltage strapping pin: it must read low at reset. R24 holds AUDIO_EN low; it may only be driven after boot.
* D2 lets GPIO0 pull GPIO2 low for download mode despite the SD D0 pull-up. GPIO0 must stay an input at runtime.
* VBUS present: load runs from USB via D1, Q1 isolates the battery so the charger terminates correctly. SW4 cuts the load only; charging still works when off.

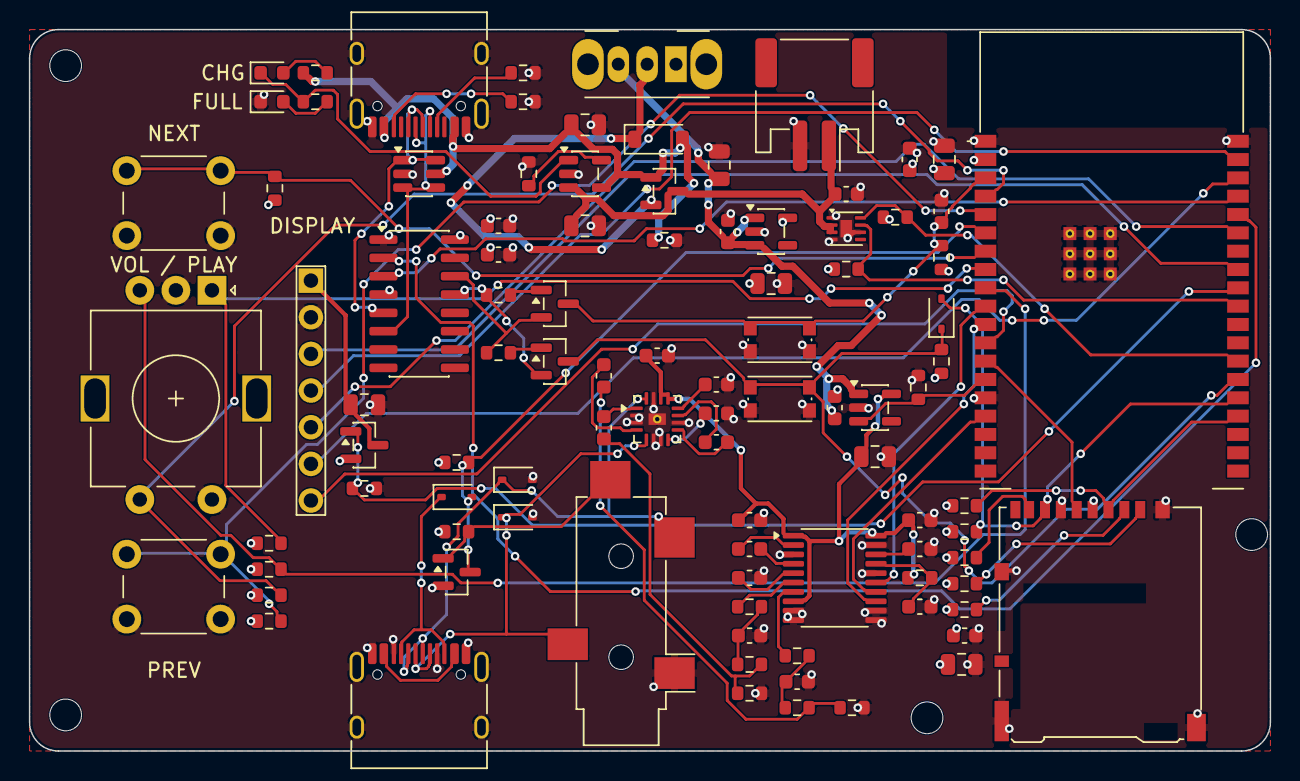
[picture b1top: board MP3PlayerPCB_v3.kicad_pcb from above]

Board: 4 copper layers, 86.0 x 50.0 mm, 100 parts (0 on the bottom side), 70 nets.

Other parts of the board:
H1, H2, H3, H4: M2; MountingHole_2.2mm_M2

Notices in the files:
README.md:
License:
TBD
